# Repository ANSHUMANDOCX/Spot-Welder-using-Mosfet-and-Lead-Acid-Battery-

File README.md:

# Spot-Welder-using-Mosfet-and-Lead-Acid-Battery
## Plan
This board is designed for spot welding 18650 batteries with a 12v 7ah battery since these battery have a short circuit current of >300A so it can be used to spot weld nickel strips by delivering shot pulses of high current.
## Why i made this 
here in india good spot welders are very expensive and designing it myself allowed me to learn about gates and high current applications.
## How to use 
Its pretty simple to use we just need to connect the battery to the board using some high guage wires around 12-10AWG and connect them to 12AWG single core copper wire for putting the welding spots.
Also the timing of the circuit can be adjusted by changing the C11.
## Parts Requried 
- 12v 7Ah Lead acid battery
- IRLB4132 Mosfet
- NE555 timer IC 

## PCB and Schematic

# BOM 

| Name                                      | Qty | Vendor | Price ($) | Links |
|-------------------------------------------|-----|--------|-----------|-------|
| ALL BOM parts mosfet, resistor, capacitors etc |     | LCSC   | 14        |       |
| Wires 12awg and 12 awg solid core         | 1   | Robu   | 5         | [Link 1](https://robu.in/product/sps-61t-250-jst-quick-terminal-rohs/)<br>[Link 2](https://robu.in/product/12awg-solid-core-insulated-wire-silicone-black/)<br>[Link 3](https://robu.in/product/high-quality-ultra-flexible-12awg-silicone-wire-black/)<br>[Link 4](https://robu.in/product/high-quality-ultra-flexible-12awg-silicone-wire-red/) |
| Lead acid Battery AMARON 12v 7ah          | 1   | Amazon | 15        |[LINK](https://www.amazon.in/Amaron-Quanta-12-AL-007/dp/B01D1JQO3I?source=ps-sl-shoppingads-lpcontext&ref_=fplfs&psc=1&smid=A20KWYYO0T79V8)      |
| PCB                                       |     | JLCPCB | 5         |       |
| **Total**                                 |     |        | **40**    |       |

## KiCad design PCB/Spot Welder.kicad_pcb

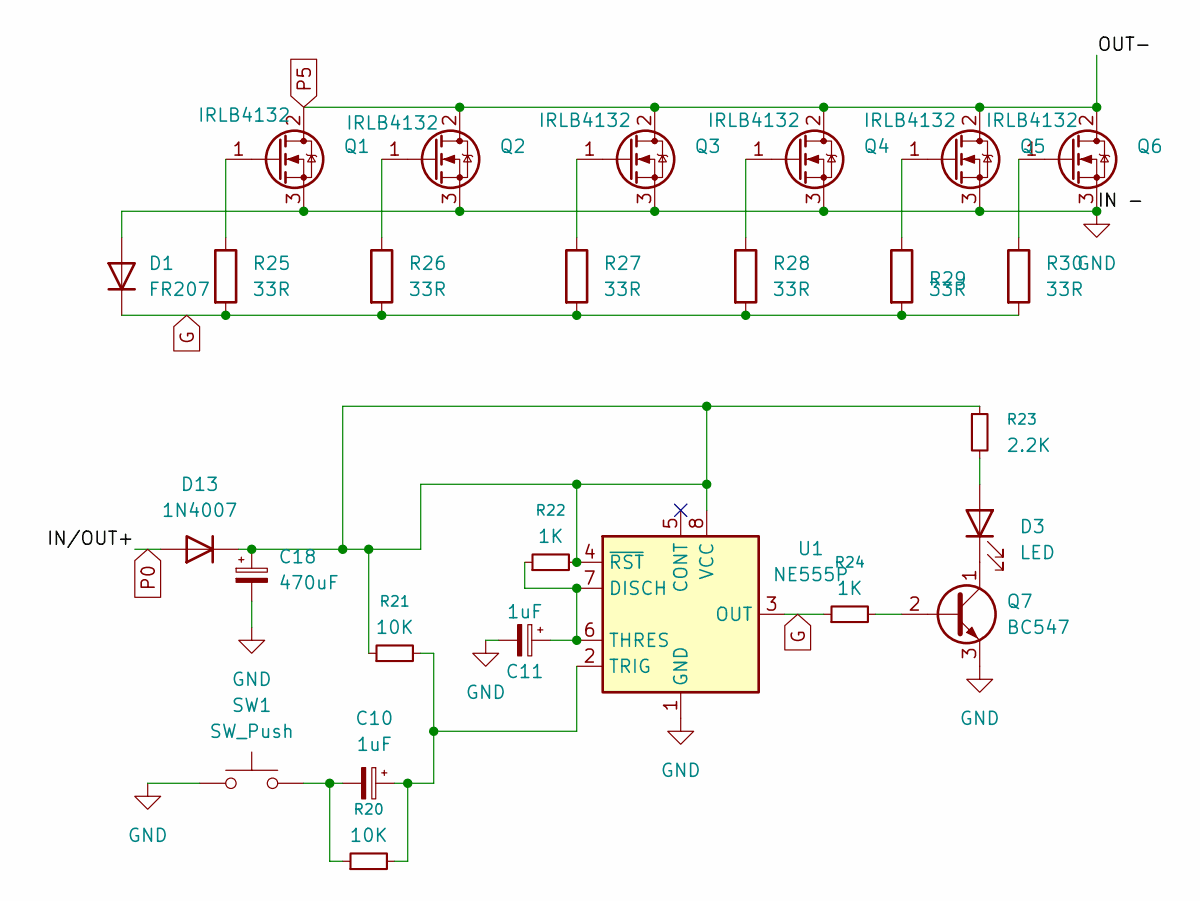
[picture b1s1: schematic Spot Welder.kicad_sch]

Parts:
C10: 1uF; CP_Radial_D5.0mm_P2.50mm
C11: 1uF; CP_Radial_D8.0mm_P2.50mm
C18: 470uF; CP_Radial_D10.0mm_P5.00mm
D1: FR207; D_DO-15_P12.70mm_Horizontal
D3: LED; LED_D3.0mm
D13: 1N4007; D_DO-15_P12.70mm_Horizontal
Q1, Q2, Q3, Q4, Q5, Q6: IRLB4132; TO-220-3_Horizontal_TabDown
Q7: BC547; TO-92_Inline
R20, R21: 10K; R_Axial_DIN0207_L6.3mm_D2.5mm_P7.62mm_Horizontal
R22, R24: 1K; R_Axial_DIN0207_L6.3mm_D2.5mm_P7.62mm_Horizontal
R23: 2.2K; R_Axial_DIN0207_L6.3mm_D2.5mm_P7.62mm_Horizontal
R25, R26, R27, R28, R29, R30: 33R; R_Axial_DIN0207_L6.3mm_D2.5mm_P7.62mm_Horizontal
SW1: SW_Push; PinHeader_1x02_P2.54mm_Vertical
U1: NE555P; DIP-8_W7.62mm

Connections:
G: D1.1 (K), R24.1, R25.2, R26.2, R27.2, R28.2, R29.2, R30.2, U1.3 (OUT)
GND: C11.2, C18.2, D1.2 (A), Q1.3 (S), Q2.3 (S), Q3.3 (S), Q4.3 (S), Q5.3 (S), Q6.3 (S), Q7.3 (E), SW1.1, U1.1 (GND)
unnamed: C10.2, R20.1, SW1.2
unnamed: D3.2 (A), R23.2
unnamed: D3.1 (K), Q7.1 (C)
unnamed: C18.1, D13.1 (K), R21.1, R22.2, R23.1, U1.4 (~RST), U1.8 (VCC)
unnamed: Q1.1 (G), R25.1
unnamed: Q2.1 (G), R26.1
unnamed: Q3.1 (G), R27.1
unnamed: Q4.1 (G), R28.1
unnamed: Q5.1 (G), R29.1
unnamed: Q6.1 (G), R30.1
unnamed: Q7.2 (B), R24.2
unnamed: C11.1, R22.1, U1.6 (THRES), U1.7 (DISCH)
unnamed: C10.1, R20.2, R21.2, U1.2 (TRIG)
P0: D13.2 (A)
P5: Q1.2 (D), Q2.2 (D), Q3.2 (D), Q4.2 (D), Q5.2 (D), Q6.2 (D)

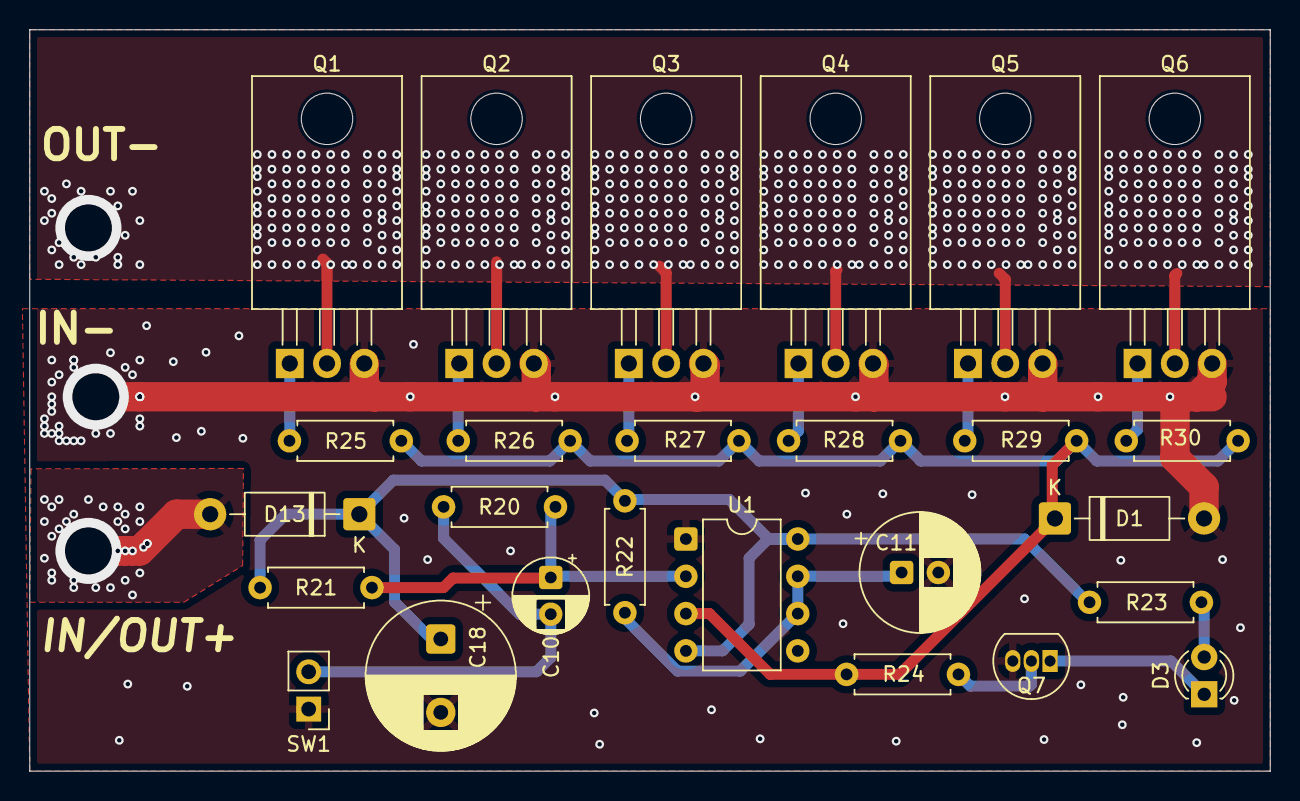
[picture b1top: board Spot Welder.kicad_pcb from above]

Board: 2 copper layers, 84.5 x 50.5 mm, 26 parts (0 on the bottom side), 16 nets.

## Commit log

2026-01-24 Add journal entries for circuit and PCB development
    Documented the progress of circuit design, PCB routing, and modifications in the journal.
2026-01-25 had uploaded the wrong journal
